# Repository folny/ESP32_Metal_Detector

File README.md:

# ESP32 Metal Detector

BLE Library https://github.com/nkolban/ESP32_BLE_Arduino

Forum http://www.geotech1.com/forums/showthread.php?24589-ESP32-Metal-detector

https://www.youtube.com/watch?v=ikg0VJCtUzE

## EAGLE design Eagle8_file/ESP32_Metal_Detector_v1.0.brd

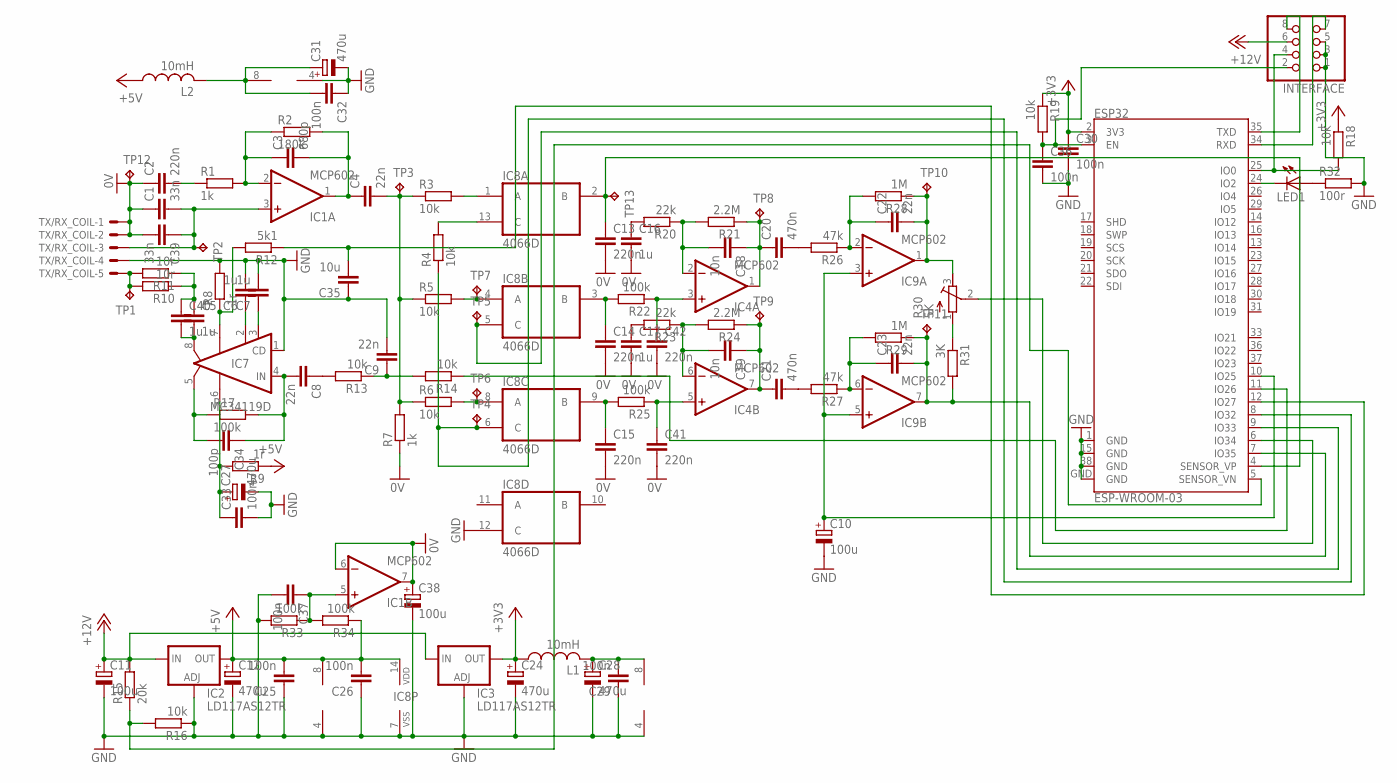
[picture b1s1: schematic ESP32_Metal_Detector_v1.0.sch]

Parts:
C1: 33n; C050-055X075
C2, C13, C14, C15, C41, C42: 220n; C1206
C3: 680p; C1206
C4, C8, C9, C22, C23: 22n; C1206
C5: 1u; C050-055X075
C6, C7, C16, C17, C40: 1u; C1206
C10, C38: 100u; SMC_B
C11: 100u; SMC_E
C12, C24, C27, C28, C31: 470u; SMC_D
C18, C19: 10n; C1206
C20, C21: 470n; C1206
C25, C26, C29, C30, C32, C33, C36, C37: 100n; C1206
C34: 100p; C1206
C35: 10u; C1206
C39: 33n; C1206
ESP32: ESP-WROOM-03
IC1, IC4, IC9: MCP602; SO08
IC2, IC3: LD117AS12TR; SOT223
IC7: MC34119D; SO08
IC8: 4066D; SO14
INTERFACE: PINHD-2X4; 2X04
L1, L2: 10mH; L5650M
LED1: LEDSML1206; SML1206
R1, R7: 1k; R1206
R2: 180k; R1206
R3, R4, R5, R6, R13, R14, R16, R18, R19: 10k; R1206
R8, R9: 1r; R1206
R10, R11: 10r; R1206
R12: 5k1; R1206
R15: 20k; R1206
R17, R22, R25, R33, R34: 100k; R1206
R20, R23: 22k; R1206
R21, R24: 2.2M; R1206
R26, R27: 47k; R1206
R28, R29: 1M; R1206
R30: 5K; RTRIM4G/J
R31: 3K; R1206
R32: 100r; R1206
TP1, TP2, TP3, TP4, TP5, TP6, TP7, TP8, TP9, TP10, TP11, TP12, TP13: TPPAD1-13; P1-13
TX/RX_COIL: 22-23-2051

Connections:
0V: C1.1, C2.1, C13.2, C14.2, C15.2, C16.2, C17.2, C38.+, C39.2, C41.2, C42.2, IC1.6 (-IN), IC1.7 (OUT), R7.1, TP12.TP, TX/RX_COIL.1, TX/RX_COIL.2
+3V3: C24.+, C30.1, ESP32.2 (3V3), IC3.4 (OUT), L1.1, R18.1, R19.1
+5V: C12.+, C25.2, C26.2, IC2.4 (OUT), IC4.8 (V+), IC8.14 (VDD), L2.1, R9.1, R34.1
+12V: C11.+, IC2.3 (IN), IC3.3 (IN), INTERFACE.6, R15.2
GND: C6.2, C7.2, C9.2, C10.-, C11.-, C12.-, C24.-, C25.1, C26.1, C27.-, C28.-, C29.1, C30.2, C31.-, C32.1, C33.2, C35.1, C36.2, C37.2, C38.-, ESP32.1 (GND), ESP32.15 (GND), ESP32.38 (GND), ESP32.GND, IC1.4 (V-), IC2.1 (ADJ), IC3.1 (ADJ), IC4.4 (V-), IC7.1 (CD), IC8.7 (VSS), IC8.12 (C), IC9.4 (V-), INTERFACE.1, INTERFACE.3, INTERFACE.5, R8.2, R16.1, R32.2, R33.2, TX/RX_COIL.4
unnamed: C3.2, C4.1, IC1.1 (OUT), R2.2
unnamed: R30.1 (A), R31.1
unnamed: C1.2, C39.1, IC1.3 (+IN), TP2.TP, TX/RX_COIL.3
unnamed: C2.2, R1.1
unnamed: C3.1, IC1.2 (-IN), R1.2, R2.1
unnamed: ESP32.8 (IO32), IC8.6 (C), R4.1, TP4.TP
unnamed: IC8.1 (A), R3.2
unnamed: IC8.8 (A), R6.2, TP6.TP
unnamed: C4.2, R3.1, R5.1, R6.1, R7.2, TP3.TP
unnamed: C22.2, IC9.1 (OUT), R28.1, R30.3 (E), TP10.TP
unnamed: IC8.13 (C), R4.2
unnamed: C5.2, C40.2, IC7.8 (VO2)
unnamed: C5.1, C40.1, R10.1, R11.1
unnamed: C15.1, IC8.9 (B), R25.2
unnamed: C27.+, C33.1, IC7.6 (VCC), R9.2
unnamed: IC7.7 (GND), R8.1, R12.2
unnamed: C6.1, IC7.2 (FC2)
unnamed: C7.1, IC7.3 (FC1)
unnamed: C8.2, C34.1, IC7.4 (IN), R17.2
unnamed: C8.1, R13.2
unnamed: C9.1, R13.1, R14.2
unnamed: ESP32.11 (IO26), R14.1
unnamed: C28.+, C29.2, IC9.8 (V+), L1.2
unnamed: IC8.4 (A), R5.2, TP7.TP
unnamed: C14.1, IC8.3 (B), R22.2
unnamed: ESP32.5 (SENSOR_VN), R15.1, R16.2
unnamed: ESP32.9 (IO33), IC8.5 (C), TP5.TP
unnamed: ESP32.6 (IO34), R30.2 (S)
unnamed: C13.1, ESP32.4 (SENSOR_VP), IC8.2 (B), TP13.TP
unnamed: C31.+, C32.2, IC1.8 (V+), L2.2
unnamed: C34.2, IC7.5 (VO1), R17.1
unnamed: C18.1, C20.1, IC4.1 (OUT), R21.1, TP8.TP
unnamed: C18.2, IC4.2 (-IN), R20.1, R21.2
unnamed: C19.2, IC4.6 (-IN), R23.1, R24.2
unnamed: C35.2, ESP32.12 (IO27), R12.1
unnamed: C42.1, IC4.3 (+IN), R22.1
unnamed: C41.1, IC4.5 (+IN), R25.1
unnamed: C20.2, R26.2
unnamed: C21.2, R27.2
unnamed: C23.1, IC9.6 (-IN), R27.1, R29.2
unnamed: C22.1, IC9.2 (-IN), R26.1, R28.2
unnamed: ESP32.25 (IO0), INTERFACE.4, R18.2
unnamed: C23.2, ESP32.7 (IO35), IC9.7 (OUT), R29.1, R31.2, TP11.TP
unnamed: C10.+, ESP32.10 (IO25), IC9.3 (+IN), IC9.5 (+IN)
unnamed: C19.1, C21.1, IC4.7 (OUT), R24.1, TP9.TP
unnamed: LED1.A, R32.1
unnamed: C36.1, ESP32.3 (EN), INTERFACE.2, R19.2
unnamed: C16.1, R20.2
unnamed: C17.1, R23.2
unnamed: R10.2, R11.2, TP1.TP, TX/RX_COIL.5
unnamed: ESP32.24 (IO2), LED1.C
unnamed: C37.1, IC1.5 (+IN), R33.1, R34.2
unnamed: ESP32.35 (TXD), INTERFACE.8
unnamed: ESP32.34 (RXD), INTERFACE.7

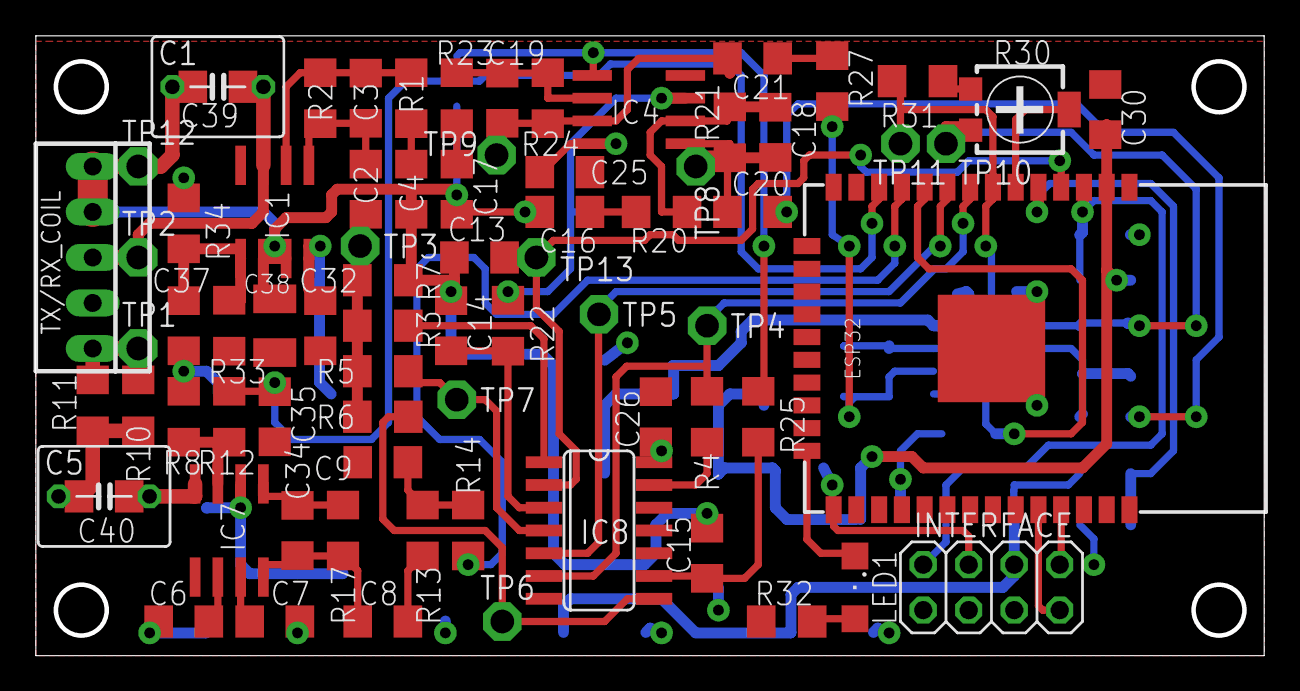
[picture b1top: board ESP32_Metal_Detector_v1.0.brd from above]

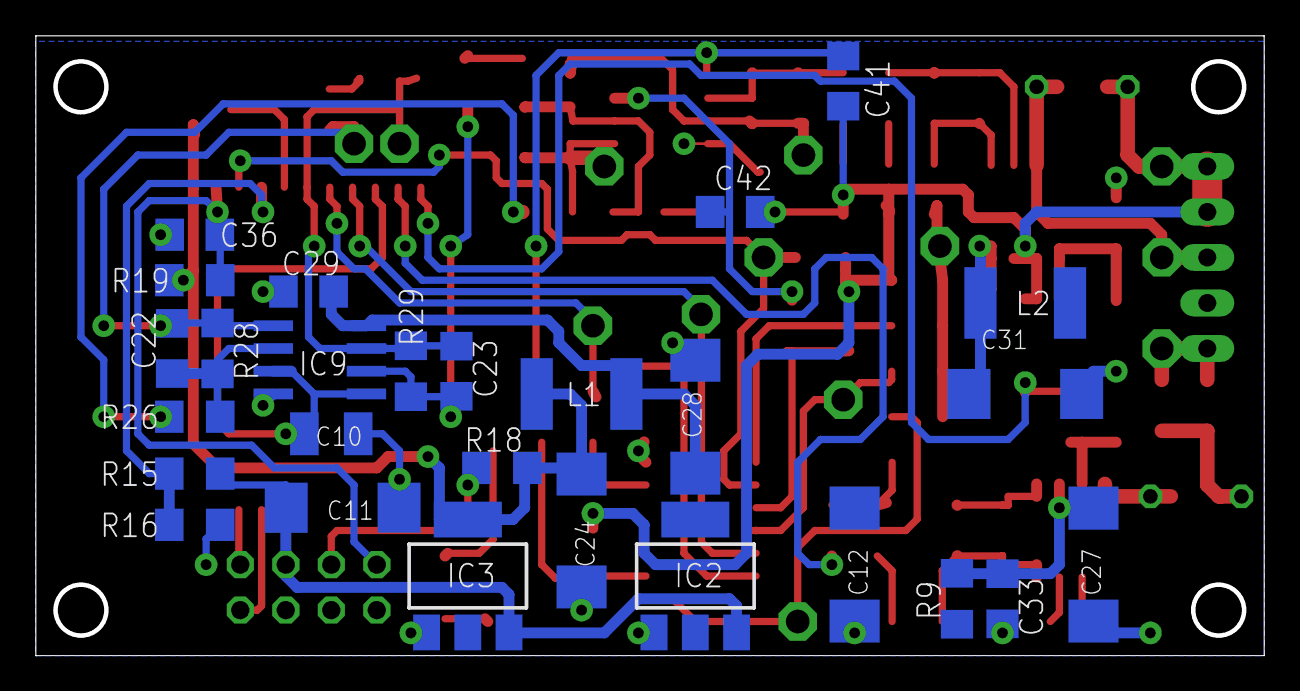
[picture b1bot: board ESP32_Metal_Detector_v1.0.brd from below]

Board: 2 copper layers, 68.6 x 34.6 mm, 102 parts (27 on the bottom side), 59 nets.

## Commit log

2022-12-15 Upload KiCad Files
2022-12-16 Upload Schematic and PCB files
2022-12-16 Add BOM file
2022-12-20 Via improvement
